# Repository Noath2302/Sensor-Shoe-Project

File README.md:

# Sensor-Shoe-Project
Sensor-Shoe Project FRA-UAS 2019 VGU EEIT2015 Truong Thanh Toan
Deadline around 18-20/08

25/06/2019
-- Create a github repository

Work to do:
-- Make the full PCB for testing
-- Optimize the usage of sensor system
-- Adding also the thesis to the repository

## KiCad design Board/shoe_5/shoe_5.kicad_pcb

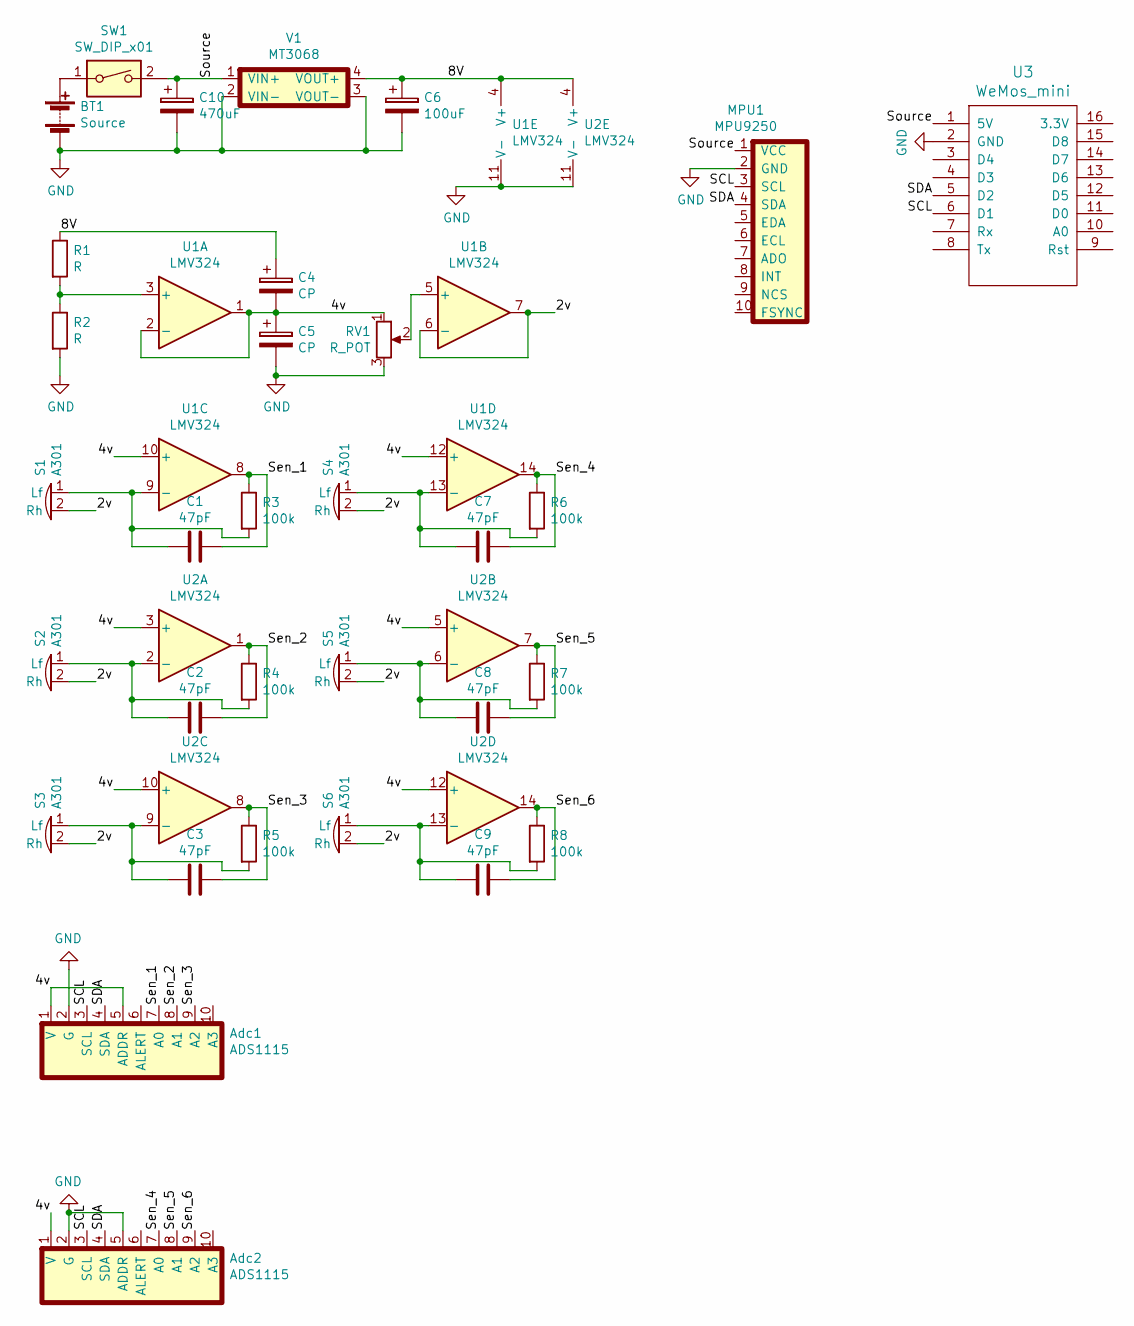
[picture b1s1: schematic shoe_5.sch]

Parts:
Adc1, Adc2: ADS1115; PinSocket_1x10_P2.54mm_Vertical
BT1: Source; PinSocket_2x01_P2.54mm_Vertical
C1, C2, C3, C7, C8, C9: 47pF; C_0805_2012Metric
C4, C5: CP; CP_Radial_Tantal_D4.5mm_P5.00mm
C6: 100uF; CP_Radial_D5.0mm_P2.50mm
C10: 470uF; CP_Radial_D5.0mm_P2.50mm
MPU1: MPU9250; PinSocket_1x10_P2.54mm_Vertical
R1, R2: R; R_0805_2012Metric
R3, R4, R5, R6, R7, R8: 100k; R_0805_2012Metric
RV1: R_POT; Potentiometer_Bourns_3006P_Horizontal
S1, S2, S3, S4, S5, S6: A301; PinSocket_1x02_P2.00mm_Horizontal
SW1: SW_DIP_x01; SW_small
U1, U2: LMV324; SOIC-14_3.9x8.7mm_P1.27mm
U3: WeMos_mini; wemos-d1-mini-with-pin-header-and-connector
V1: MT3068; MT3608_module

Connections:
/2v: S1.2 (Rh), S2.2 (Rh), S3.2 (Rh), S4.2 (Rh), S5.2 (Rh), S6.2 (Rh), U1.6 (-), U1.7
/4v: Adc1.1 (V), Adc1.5 (ADDR), Adc2.1 (V), C4.2, C5.1, RV1.1, U1.1, U1.2 (-), U1.10 (+), U1.12 (+), U2.3 (+), U2.5 (+), U2.10 (+), U2.12 (+)
/8V: C4.1, C6.1, R1.1, U1.4 (V+), U2.4 (V+), V1.4 (VOUT+)
/SCL: Adc1.3 (SCL), Adc2.3 (SCL), MPU1.3 (SCL), U3.6 (D1)
/SDA: Adc1.4 (SDA), Adc2.4 (SDA), MPU1.4 (SDA), U3.5 (D2)
/Sen_1: Adc1.7 (A0), C1.1, R3.1, U1.8
/Sen_2: Adc1.8 (A1), C2.1, R4.1, U2.1
/Sen_3: Adc1.9 (A2), C3.1, R5.1, U2.8
/Sen_4: Adc2.7 (A0), C7.1, R6.1, U1.14
/Sen_5: Adc2.8 (A1), C8.1, R7.1, U2.7
/Sen_6: Adc2.9 (A2), C9.1, R8.1, U2.14
/Source: C10.1, MPU1.1 (VCC), SW1.2, U3.1 (5V), V1.1 (VIN+)
GND: Adc1.2 (G), Adc2.2 (G), Adc2.5 (ADDR), BT1.2 (-), C5.2, C6.2, C10.2, MPU1.2 (GND), R2.2, RV1.3, U1.11 (V-), U2.11 (V-), U3.2 (GND), V1.2 (VIN-), V1.3 (VOUT-)
unnamed: BT1.1 (+), SW1.1
unnamed: C1.2, R3.2, S1.1 (Lf), U1.9 (-)
unnamed: C2.2, R4.2, S2.1 (Lf), U2.2 (-)
unnamed: C3.2, R5.2, S3.1 (Lf), U2.9 (-)
unnamed: C7.2, R6.2, S4.1 (Lf), U1.13 (-)
unnamed: C8.2, R7.2, S5.1 (Lf), U2.6 (-)
unnamed: C9.2, R8.2, S6.1 (Lf), U2.13 (-)
unnamed: R1.2, R2.1, U1.3 (+)
unnamed: RV1.2, U1.5 (+)

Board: 2 copper layers, 34 parts (0 on the bottom side), 22 nets, no tracks yet.

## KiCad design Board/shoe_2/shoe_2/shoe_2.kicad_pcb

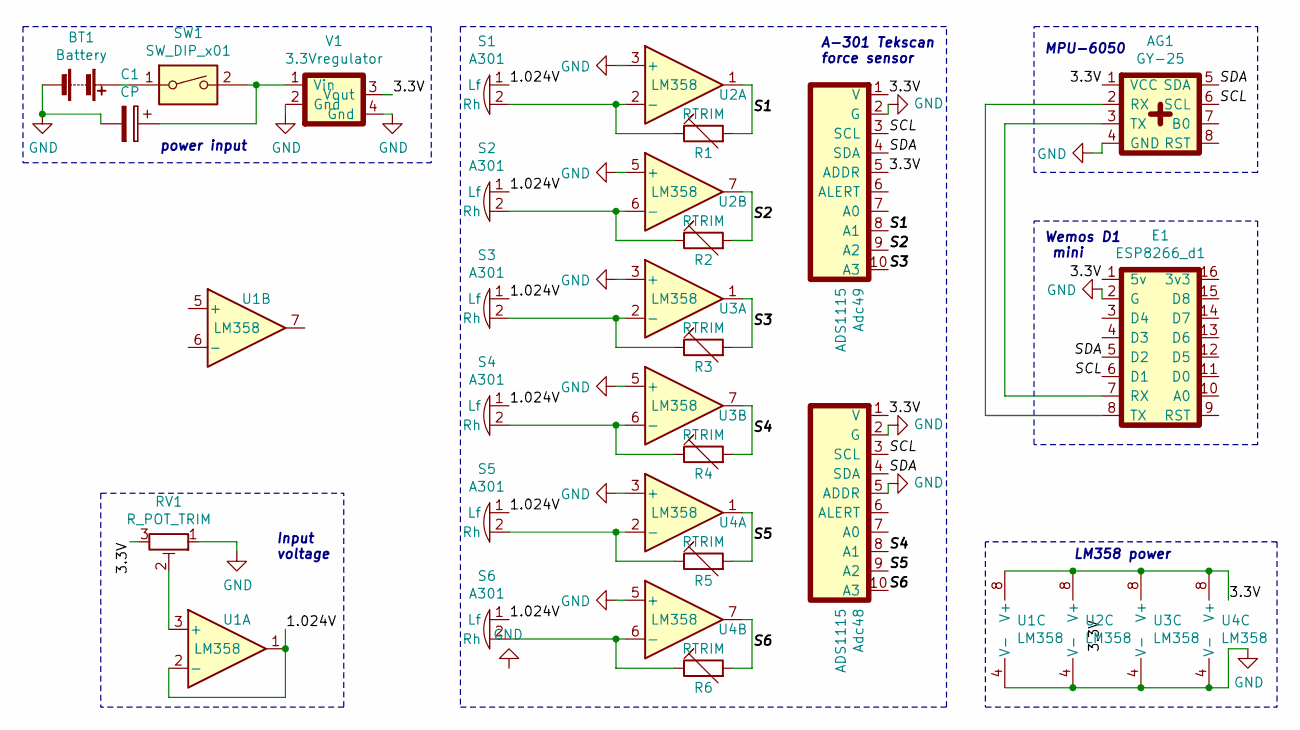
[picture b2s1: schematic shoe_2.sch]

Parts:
AG1: GY-25; PinSocket_2x04_P2.00mm_Horizontal
Adc48, Adc49: ADS1115; PinHeader_2x05_P2.00mm_Horizontal
BT1: Battery; BatteryHolder_Keystone_2462_2xAA
C1: CP; CP_Radial_D4.0mm_P2.00mm
E1: ESP8266_d1; PinSocket_2x08_P1.27mm_Horizontal
R1, R2, R3, R4, R5, R6: RTRIM; R_Axial_DIN0204_L3.6mm_D1.6mm_P5.08mm_Horizontal
RV1: R_POT_TRIM; Potentiometer_Bourns_3296X_Horizontal
S1, S2, S3, S4, S5, S6: A301; LED_Oval_W5.2mm_H3.8mm
SW1: SW_DIP_x01; JST_XH_S02B-XH-A_1x02_P2.50mm_Horizontal
U1, U2, U3, U4: LM358; DIP-8_W7.62mm_Socket_LongPads
V1: 3.3Vregulator; SW_TH_Tactile_Omron_B3F-10xx

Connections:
/1.024V: S1.1 (Lf), S2.1 (Lf), S3.1 (Lf), S4.1 (Lf), S5.1 (Lf), S6.1 (Lf), U1.1, U1.2 (-)
/3.3V: AG1.1 (VCC), Adc48.1 (V), Adc49.1 (V), Adc49.5 (ADDR), E1.1 (5v), RV1.3, U1.8 (V+), U2.8 (V+), U3.8 (V+), U4.8 (V+), V1.3 (Vout)
/S1: Adc49.8 (A1), R1.2, U2.1
/S2: Adc49.9 (A2), R2.2, U2.7
/S3: Adc49.10 (A3), R3.2, U3.1
/S4: Adc48.8 (A1), R4.2, U3.7
/S5: Adc48.9 (A2), R5.2, U4.1
/S6: Adc48.10 (A3), R6.2, U4.7
/SCL: AG1.6 (SCL), Adc48.3 (SCL), Adc49.3 (SCL), E1.6 (D1)
/SDA: AG1.5 (SDA), Adc48.4 (SDA), Adc49.4 (SDA), E1.5 (D2)
GND: AG1.4 (GND), Adc48.2 (G), Adc48.5 (ADDR), Adc49.2 (G), BT1.2 (-), C1.2, E1.2 (G), RV1.1, U1.4 (V-), U2.3 (+), U2.4 (V-), U2.5 (+), U3.3 (+), U3.4 (V-), U3.5 (+), U4.3 (+), U4.4 (V-), U4.5 (+), V1.2 (Gnd), V1.4 (Gnd)
unnamed: AG1.2 (RX), E1.8 (TX)
unnamed: AG1.3 (TX), E1.7 (RX)
unnamed: BT1.1 (+), SW1.1
unnamed: C1.1, SW1.2, V1.1 (Vin)
unnamed: R1.1, S1.2 (Rh), U2.2 (-)
unnamed: R2.1, S2.2 (Rh), U2.6 (-)
unnamed: R3.1, S3.2 (Rh), U3.2 (-)
unnamed: R4.1, S4.2 (Rh), U3.6 (-)
unnamed: R5.1, S5.2 (Rh), U4.2 (-)
unnamed: R6.1, S6.2 (Rh), U4.6 (-)
unnamed: RV1.2, U1.3 (+)

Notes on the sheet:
power input
Input voltage
LM358 power
MPU-6050
A-301 Tekscan force sensor
Wemos D1 mini

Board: 2 copper layers, 25 parts (0 on the bottom side), 22 nets, no tracks yet.

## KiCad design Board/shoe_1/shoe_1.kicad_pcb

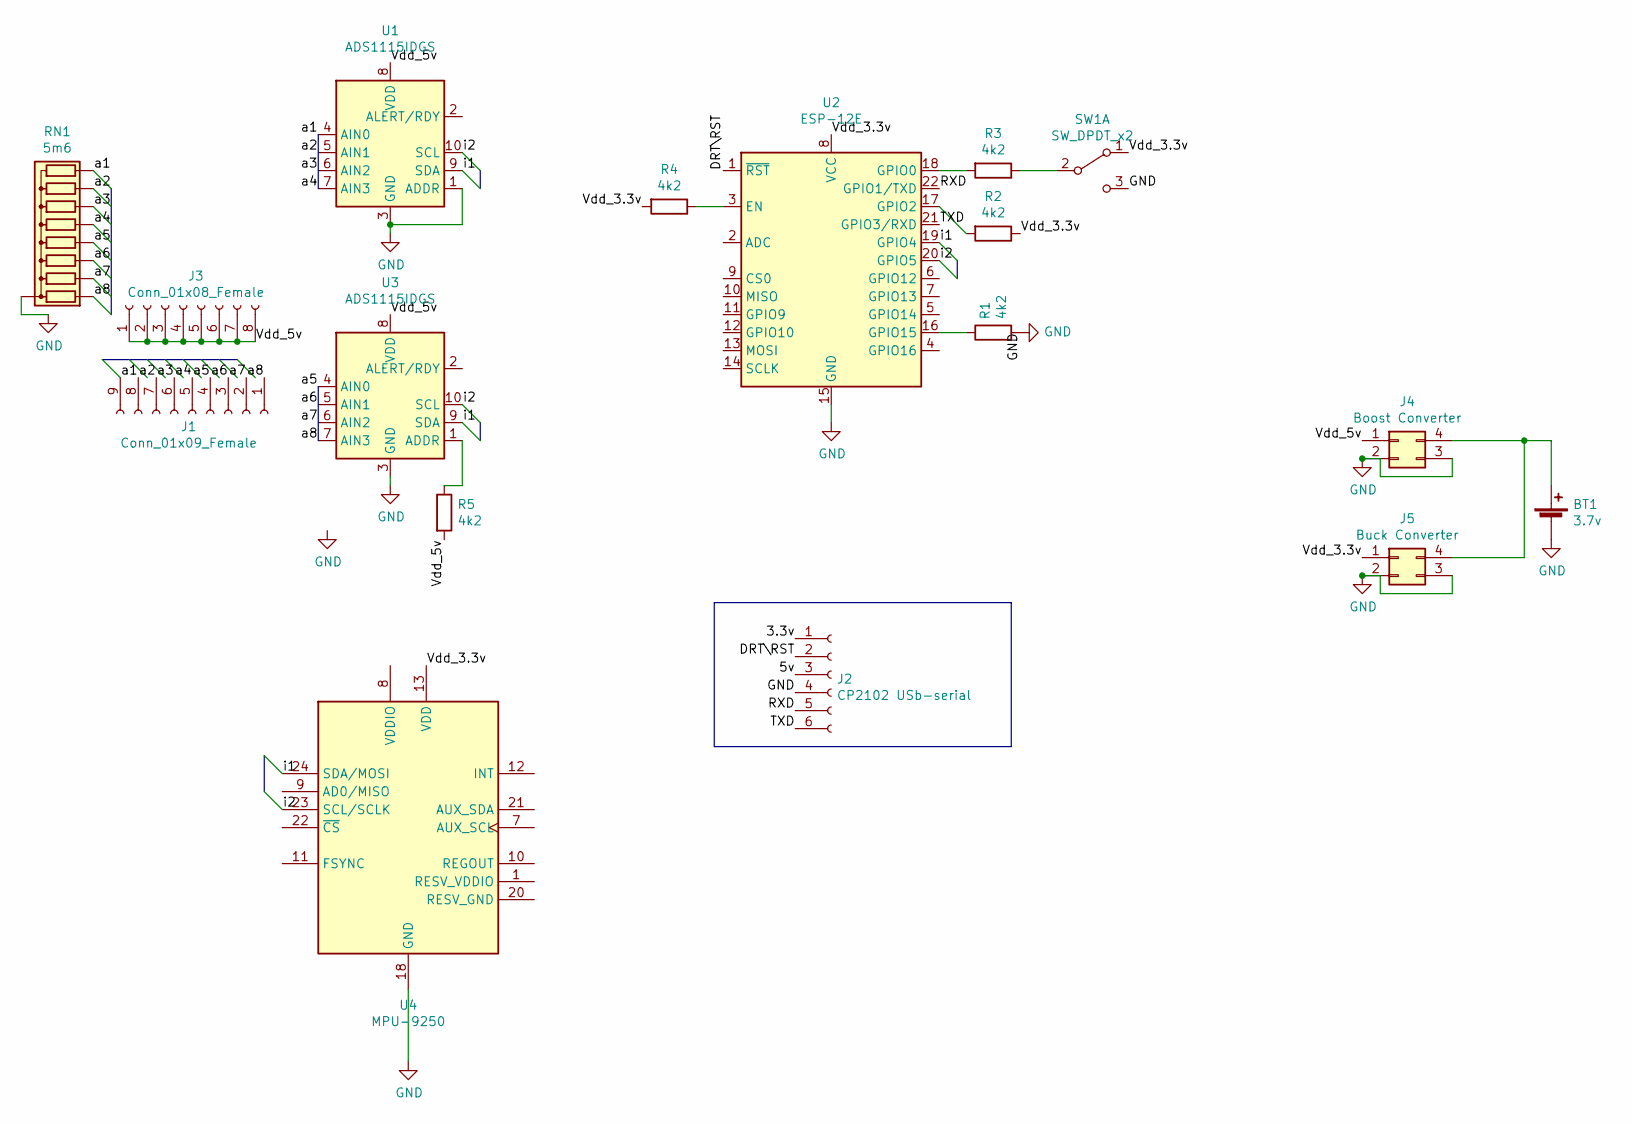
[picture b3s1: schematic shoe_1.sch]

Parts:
BT1: 3.7v; BatteryHolder_Keystone_1042_1x18650
J1: Conn_01x09_Female; JST_VH_B9P-VH-B_1x09_P3.96mm_Vertical
J2: CP2102 USb-serial; Hirose_DF13-06P-1.25DSA_1x06_P1.25mm_Vertical
J3: Conn_01x08_Female; JST_VH_B8P-VH-B_1x08_P3.96mm_Vertical
J4: Boost Converter; PinHeader_2x02_P2.54mm_Horizontal
J5: Buck Converter; PinHeader_2x02_P2.54mm_Horizontal
R1, R2, R3, R4, R5: 4k2; R_Axial_DIN0204_L3.6mm_D1.6mm_P5.08mm_Horizontal
RN1: 5m6; R_Array_SIP9
SW1: SW_DPDT_x2; SW_CuK_JS202011CQN_DPDT_Straight
U1, U3: ADS1115IDGS; TSSOP-10_3x3mm_P0.5mm
U2: ESP-12E
U4: MPU-9250; QFN-24-1EP_3x3mm_P0.4mm_EP1.75x1.6mm_ThermalVias

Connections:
/3.3v: J2.1
/5v: J2.3
/DRT\RST: J2.2, U2.1 (~RST)
/RXD: J2.5, U2.22 (GPIO1/TXD)
/TXD: J2.6, U2.21 (GPIO3/RXD)
/Vdd_3.3v: J5.1, R2.1, R4.2, SW1.1 (A), U2.8 (VCC), U4.13 (VDD)
/Vdd_5v: J3.1, J3.2, J3.3, J3.4, J3.5, J3.6, J3.7, J3.8, J4.1, R5.2, U1.8 (VDD), U3.8 (VDD)
/a1: J1.9, RN1.9 (R8), U1.4 (AIN0)
/a2: J1.8, RN1.8 (R7), U1.5 (AIN1)
/a3: J1.7, RN1.7 (R6), U1.6 (AIN2)
/a4: J1.6, RN1.6 (R5), U1.7 (AIN3)
/a5: J1.5, RN1.5 (R4), U3.4 (AIN0)
/a6: J1.4, RN1.4 (R3), U3.5 (AIN1)
/a7: J1.3, RN1.3 (R2), U3.6 (AIN2)
/a8: J1.2, RN1.2 (R1), U3.7 (AIN3)
/i1: U1.9 (SDA), U2.19 (GPIO4), U3.9 (SDA), U4.24 (SDA/MOSI)
/i2: U1.10 (SCL), U2.20 (GPIO5), U3.10 (SCL), U4.23 (SCL/SCLK)
GND: BT1.2 (-), J2.4, J4.2, J4.3, J5.2, J5.3, R1.2, RN1.1 (common), SW1.3 (C), U1.1 (ADDR), U1.3 (GND), U2.15 (GND), U3.3 (GND), U4.18 (GND)
unnamed: BT1.1 (+), J4.4, J5.4
unnamed: R1.1, U2.16 (GPIO15)
unnamed: R2.2, U2.17 (GPIO2)
unnamed: R3.1, SW1.2 (B)
unnamed: R3.2, U2.18 (GPIO0)
unnamed: R4.1, U2.3 (EN)
unnamed: R5.1, U3.1 (ADDR)

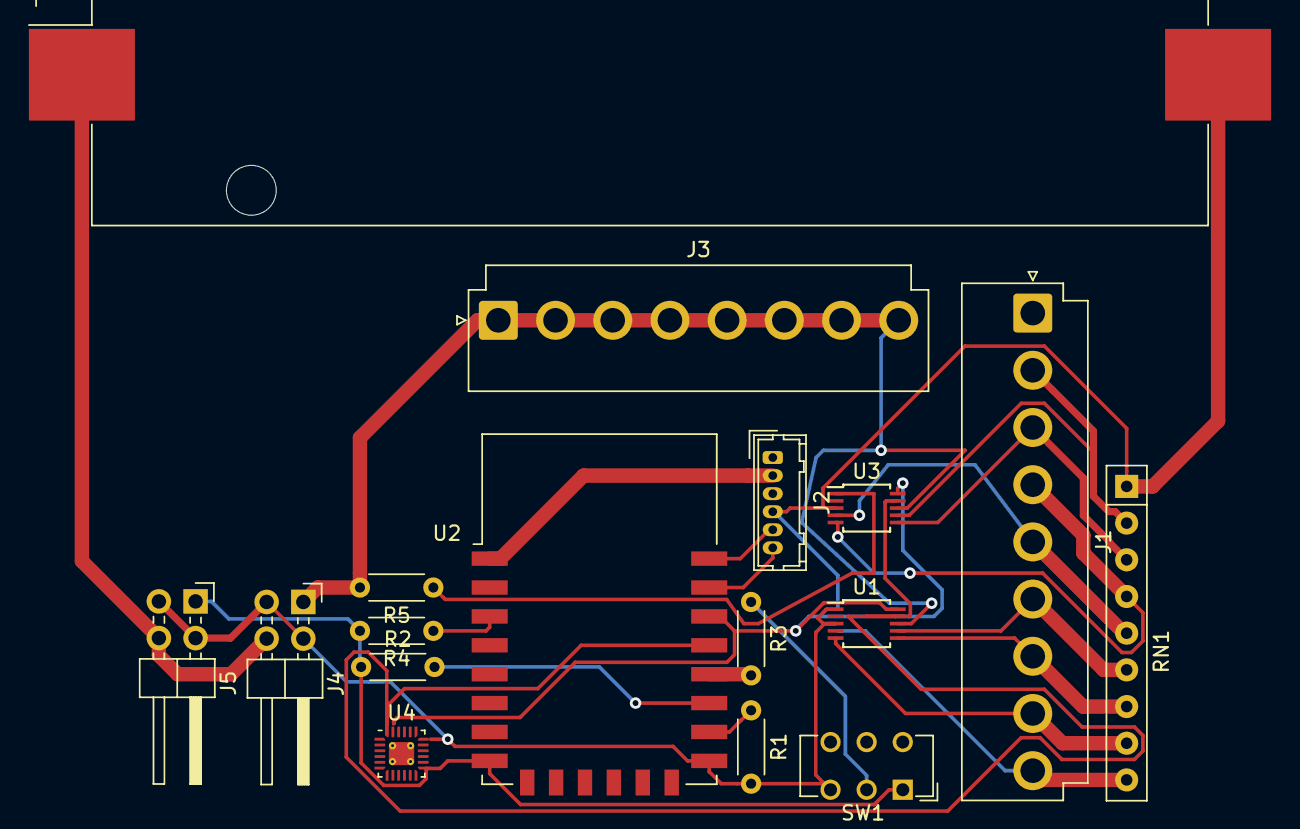
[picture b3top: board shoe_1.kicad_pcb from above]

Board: 2 copper layers, 17 parts (0 on the bottom side), 23 nets.

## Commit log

2019-06-25 initialize the repository
2019-06-25 add shoe_5 current board design
2019-07-01 please do more wiring
2019-07-18 checking day 18/07
2019-07-18 checking day 18/07 - Eagle board update
2019-11-06 adding license
